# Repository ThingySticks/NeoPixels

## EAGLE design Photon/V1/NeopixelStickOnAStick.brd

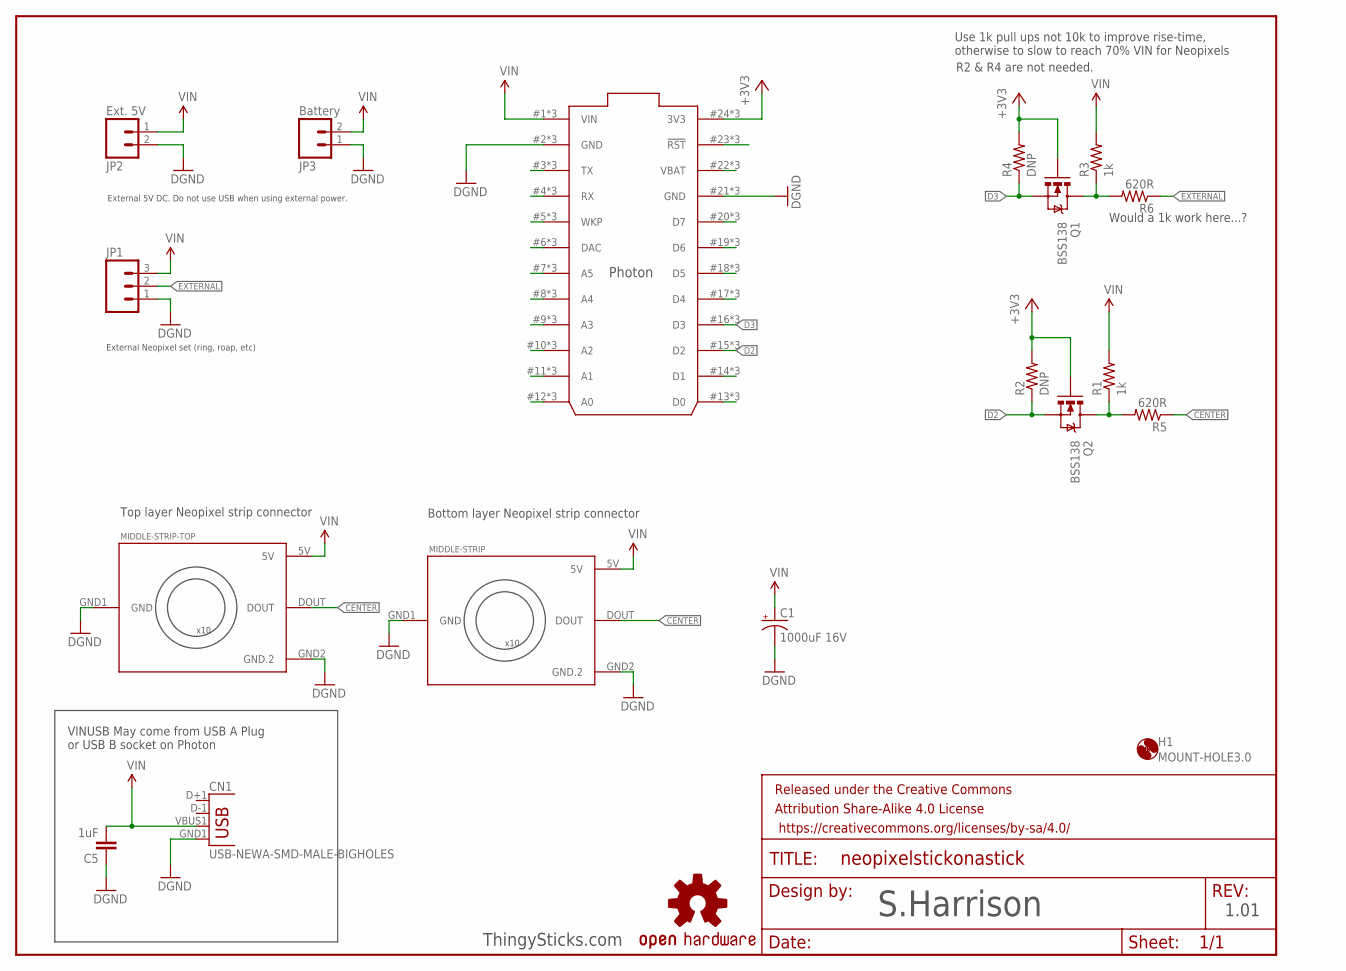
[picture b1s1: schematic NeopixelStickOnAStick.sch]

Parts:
C1: 1000uF 16V; CPOL-RADIAL-1000UF-25V
C5: 1uF; 0805
CN1: USB-NEWA-SMD-MALE-BIGHOLES; USB-A-SMT-MALE
FRAME2: FRAME-LETTER; CREATIVE_COMMONS
H1: MOUNT-HOLE3.0; 3,0
JP1: M03POLAR; MOLEX-1X3
JP2: Ext. 5V; SCREWTERMINAL-3.5MM-2
JP3: Battery; JST-2-SMD
LOGO2: OSHW-LOGOM; OSHW-LOGO-M
MIDDLE-STRIP: NEOPIXEL-STRIPBOTTOM'; NEOPIXEL-STRIP
MIDDLE-STRIP-TOP: NEOPIXEL-STRIPBOTTOM'; NEOPIXEL-STRIP
Q1, Q2: BSS138; SOT23-3
R1, R3: 1k; 1206
R2, R4: DNP; 1206
R5, R6: 620R; 1206
U$1: PHOTON_WITH_STACKABLE_HEADERS; PHOTON_STACKABLE

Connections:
+3V3: Q1.1 (G), Q2.1 (G), R2.2, R4.2, U$1.24 (3V3), U$1.#24 (3V3), U$1.@24 (3V3)
CENTER: MIDDLE-STRIP.DOUT, MIDDLE-STRIP-TOP.DOUT, R5.1
D2: Q2.2 (S), R2.1, U$1.15 (D2), U$1.#15 (D2), U$1.@15 (D2)
D3: Q1.2 (S), R4.1, U$1.16 (D3), U$1.#16 (D3), U$1.@16 (D3)
EXTERNAL: JP1.2, R6.1
GND: C1.-, C5.1, CN1.GND1 (GND), JP1.1, JP2.2, JP3.1 (2), MIDDLE-STRIP.GND1 (GND), MIDDLE-STRIP.GND2 (GND.2), MIDDLE-STRIP-TOP.GND1 (GND), MIDDLE-STRIP-TOP.GND2 (GND.2), U$1.2 (GND), U$1.21 (GND), U$1.#2 (GND), U$1.#21 (GND), U$1.@2 (GND), U$1.@21 (GND)
unnamed: U$1.13 (D0), U$1.#13 (D0), U$1.@13 (D0)
unnamed: U$1.14 (D1), U$1.#14 (D1), U$1.@14 (D1)
unnamed: Q1.3 (D), R3.1, R6.2
unnamed: Q2.3 (D), R1.1, R5.2
unnamed: U$1.17 (D4), U$1.#17 (D4), U$1.@17 (D4)
unnamed: U$1.18 (D5), U$1.#18 (D5), U$1.@18 (D5)
unnamed: U$1.19 (D6), U$1.#19 (D6), U$1.@19 (D6)
unnamed: U$1.20 (D7), U$1.#20 (D7), U$1.@20 (D7)
unnamed: U$1.22 (VBAT), U$1.#22 (VBAT), U$1.@22 (VBAT)
unnamed: U$1.23 (!RST), U$1.#23 (!RST), U$1.@23 (!RST)
unnamed: U$1.3 (TX), U$1.#3 (TX), U$1.@3 (TX)
unnamed: U$1.4 (RX), U$1.#4 (RX), U$1.@4 (RX)
unnamed: U$1.5 (WKP), U$1.#5 (WKP), U$1.@5 (WKP)
unnamed: U$1.6 (DAC), U$1.#6 (DAC), U$1.@6 (DAC)
unnamed: U$1.7 (A5), U$1.#7 (A5), U$1.@7 (A5)
unnamed: U$1.8 (A4), U$1.#8 (A4), U$1.@8 (A4)
unnamed: U$1.9 (A3), U$1.#9 (A3), U$1.@9 (A3)
unnamed: U$1.10 (A2), U$1.#10 (A2), U$1.@10 (A2)
unnamed: U$1.11 (A1), U$1.#11 (A1), U$1.@11 (A1)
unnamed: U$1.12 (A0), U$1.#12 (A0), U$1.@12 (A0)
VIN: C1.+, C5.2, CN1.VBUS1 (VBUS), JP1.3, JP2.1, JP3.2 (1), MIDDLE-STRIP.5V, MIDDLE-STRIP-TOP.5V, R1.2, R3.2, U$1.1 (VIN), U$1.#1 (VIN), U$1.@1 (VIN)

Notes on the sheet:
VINUSB May come from USB A Plug or USB B socket on Photon
External 5V DC. Do not use USB when using external power.
External Neopixel set (ring, roap, etc)
Use 1k pull ups not 10k to improve rise-time, otherwise to slow to reach 70% VIN for Neopixels
Would a 1k work here...?
R2 & R4 are not needed.
S.Harrison
1.01
ThingySticks.com
Top layer Neopixel strip connector
Bottom layer Neopixel strip connector

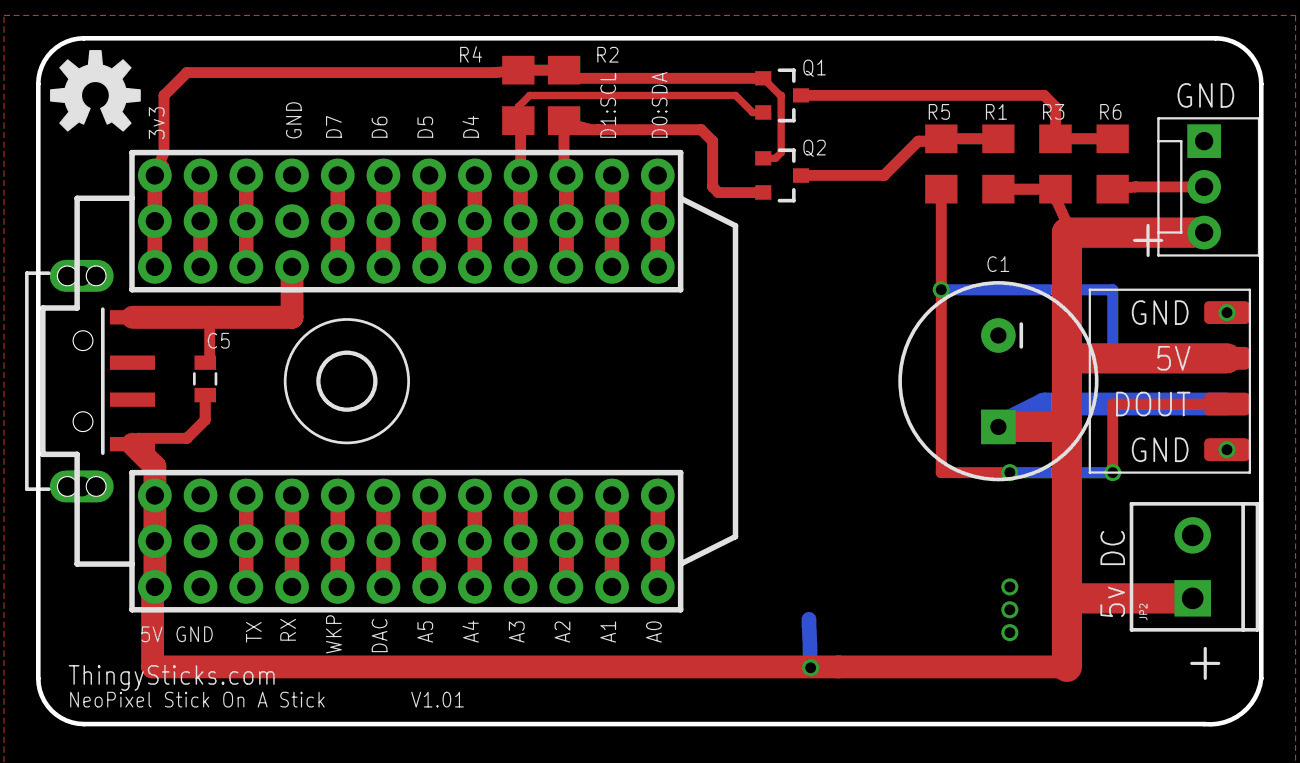
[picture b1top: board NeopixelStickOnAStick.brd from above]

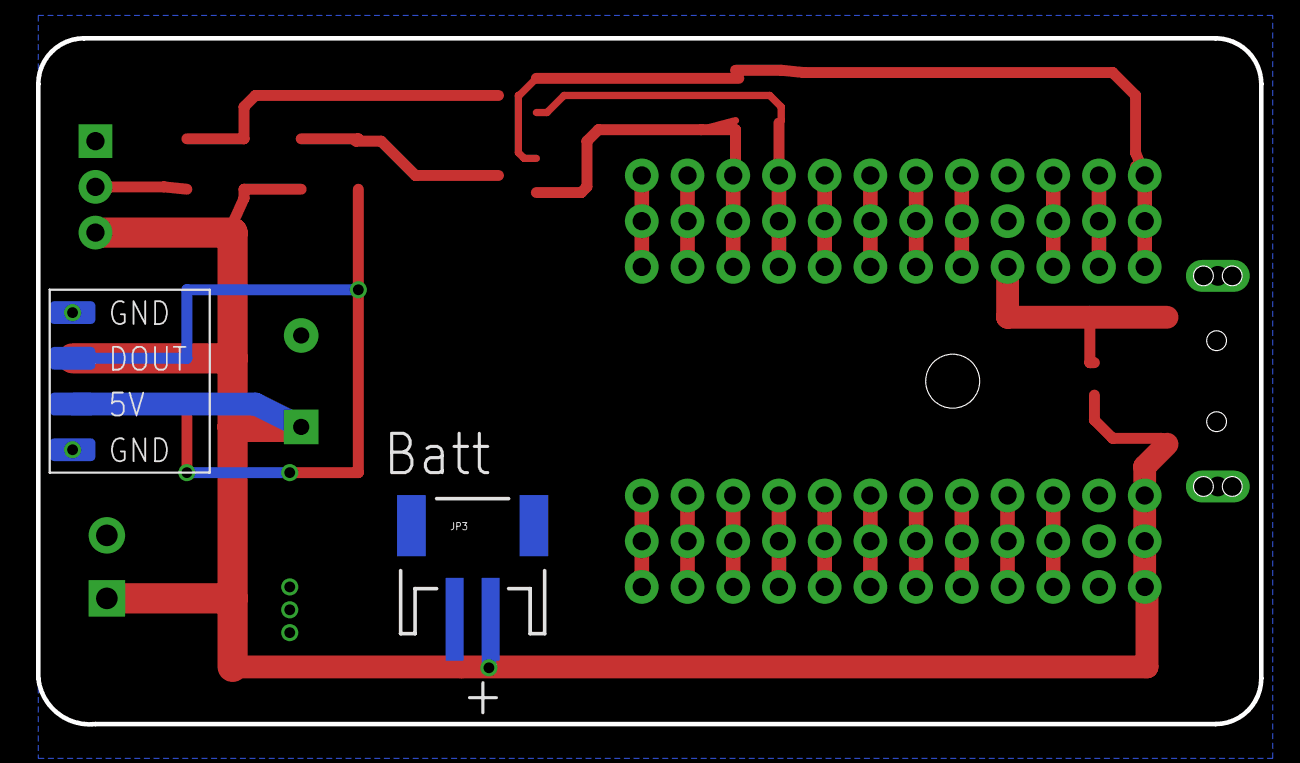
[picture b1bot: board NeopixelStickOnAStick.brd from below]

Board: 2 copper layers, 67.9 x 38.1 mm, 20 parts (2 on the bottom side), 27 nets.

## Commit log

2016-02-28 Added first version of Neopixel ThingyStick
2016-02-28 Added gitignore
2016-02-29 Removed incorrect "All through hole parts..." message from PCB.

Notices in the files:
parts and their libraries:
SparkFun-Connectors: Licensing: Creative Commons ShareAlike 4.0 International - https://creativecommons.org/licenses/by-sa/4.0
SparkFun-Aesthetics: Released under the Creative Commons Attribution Share-Alike 4.0 License
SparkFun-Aesthetics: https://creativecommons.org/licenses/by-sa/4.0
